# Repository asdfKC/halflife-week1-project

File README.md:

# Final design

### halflife-week1-project
For this project, I made a Macropad!

My components used are listed in BOM.md 

 This is an image of the 3d view of the PCB

This is an image of the PCB Gerber files!

This is my first pcb ever!

## GPIO USAGE:
It starts at GPIO0

## Key layout

| | Col 1 | Col 2 | Col 3 | Col 4 | Col 5 | Col 6 |
|---|---|---|---|---|---|---|
| **Row 1** | Ctrl+C | Ctrl+V | Ctrl+X | Ctrl+Z | Super+L | Mute |
| **Row 2** | Print Screen | F11 | Vol− | Vol+ | Up | Enter |
| **Row 3** | Previous | Play/Pause | Next | Left | Down | Right |

Switches are numbered SW1–SW18 and wired to GP0–GP17. Row 1 is SW1–SW6, row 2 is SW7, SW9, SW11, SW13, SW15, SW17, and row 3 is SW8, SW10, SW12, SW14, SW16, SW18.

The middle goes in numerical order.

## Firmware =D
The firmware is in 'firmware/code.py.' It uses KMK on CircuitPython.

## FLASHING INSTRUCTIONS
firmware/FLASHINSTRUCTIONS.md

## Switch plate :D

A pretty basic and simple plate is included in the plate/ directory. It has 18 cutouts that match the PCB, each the size of a standard MX switch cutout. The outline is in plate/Plates/plate_Edge_Cuts.dxf

I provided an STL file in the plate/ directory called plate.stl.

### Warnings

There are stray copper traces; however, they are dead and do not short the board in any way.

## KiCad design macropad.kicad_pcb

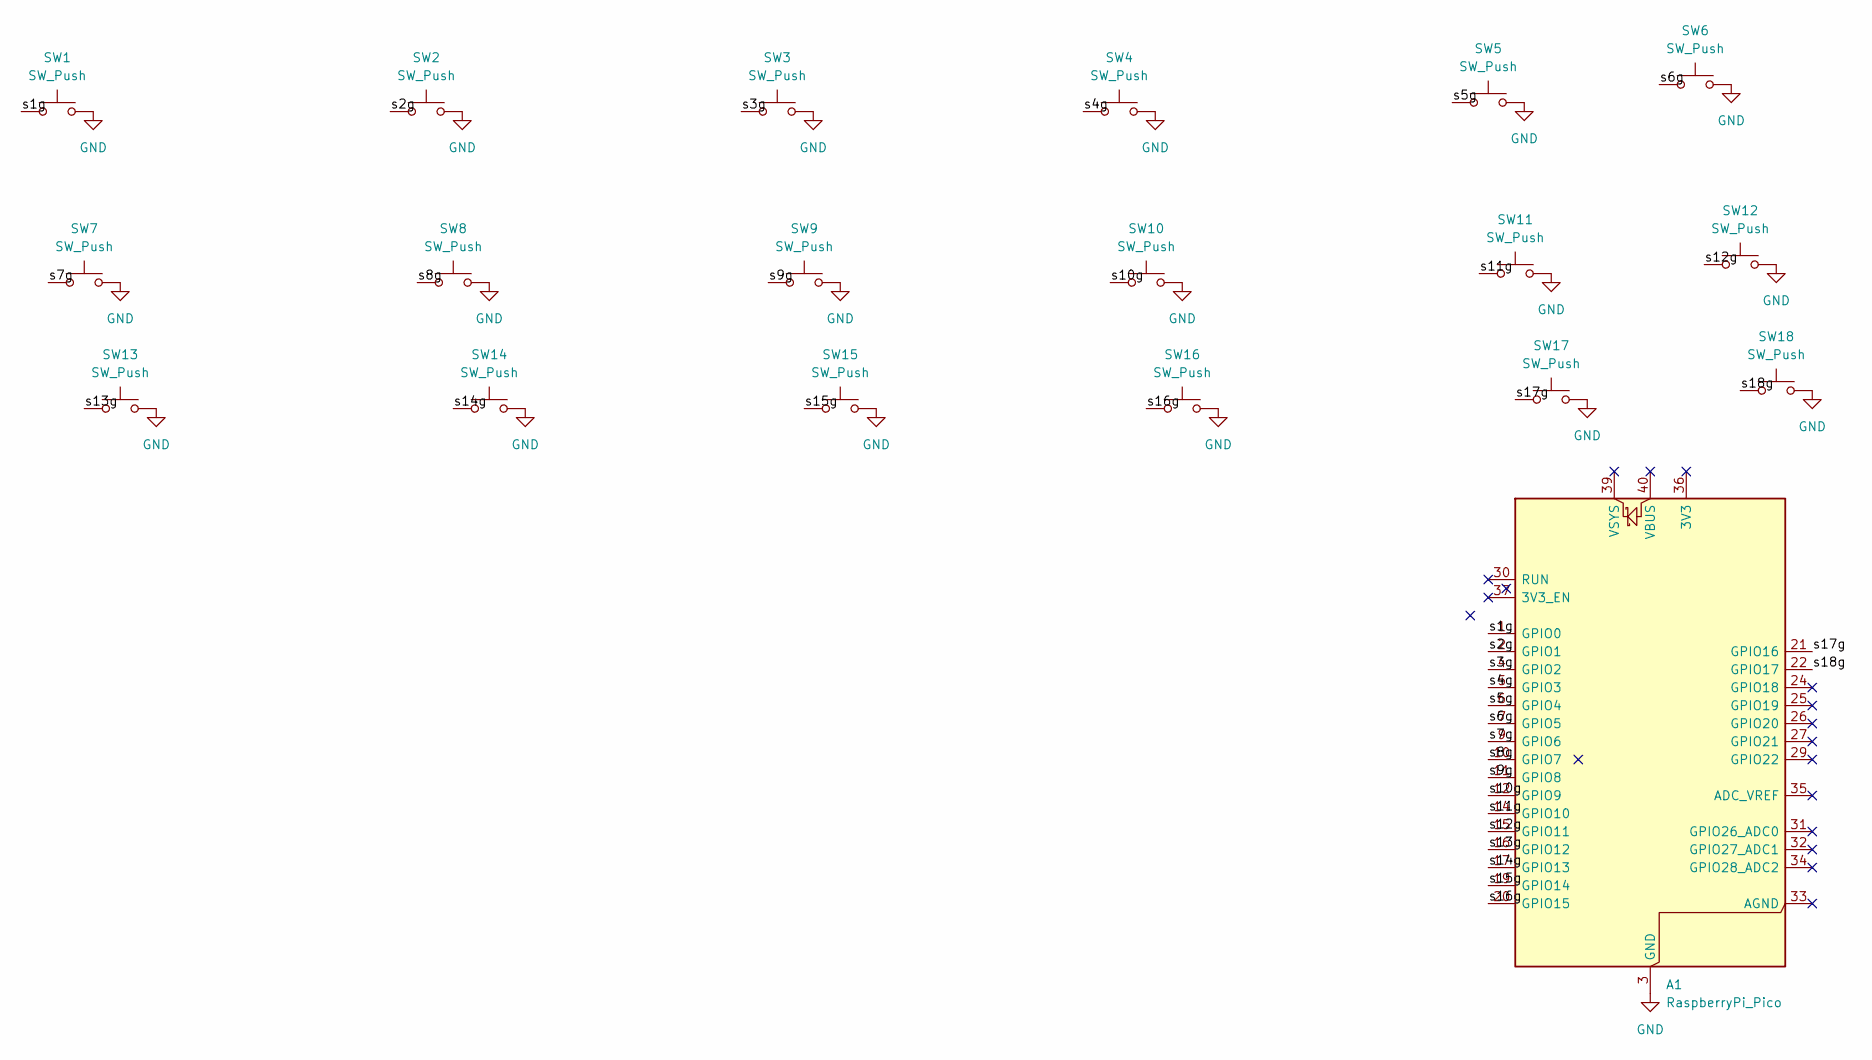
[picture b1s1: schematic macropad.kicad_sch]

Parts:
A1: RaspberryPi_Pico; RaspberryPi_Pico_Common_Unspecified
SW1, SW2, SW3, SW4, SW5, SW6, SW7, SW8, SW9, SW10, SW11, SW12, SW13, SW14, SW15, SW16, SW17, SW18: SW_Push; SW_Cherry_MX_1.00u_PCB

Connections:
/s1g: A1.1 (GPIO0), SW1.1
/s2g: A1.2 (GPIO1), SW2.1
/s3g: A1.4 (GPIO2), SW3.1
/s4g: A1.5 (GPIO3), SW4.1
/s5g: A1.6 (GPIO4), SW5.1
/s6g: A1.7 (GPIO5), SW6.1
/s7g: A1.9 (GPIO6), SW7.1
/s8g: A1.10 (GPIO7), SW8.1
/s9g: A1.11 (GPIO8), SW9.1
/s10g: A1.12 (GPIO9), SW10.1
/s11g: A1.14 (GPIO10), SW11.1
/s12g: A1.15 (GPIO11), SW12.1
/s13g: A1.16 (GPIO12), SW13.1
/s14g: A1.17 (GPIO13), SW14.1
/s15g: A1.19 (GPIO14), SW15.1
/s16g: A1.20 (GPIO15), SW16.1
/s17g: A1.21 (GPIO16), SW17.1
/s18g: A1.22 (GPIO17), SW18.1
GND: A1.3 (GND), A1.8 (GND), A1.13 (GND), A1.18 (GND), A1.23 (GND), A1.28 (GND), A1.38 (GND), SW1.2, SW2.2, SW3.2, SW4.2, SW5.2, SW6.2, SW7.2, SW8.2, SW9.2, SW10.2, SW11.2, SW12.2, SW13.2, SW14.2, SW15.2, SW16.2, SW17.2, SW18.2

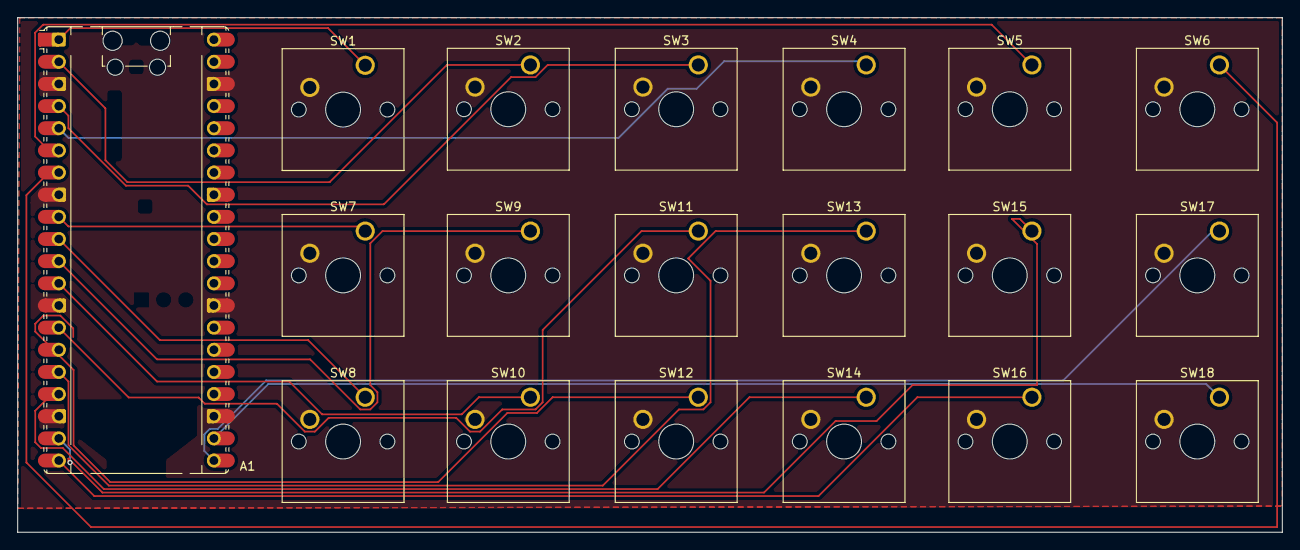
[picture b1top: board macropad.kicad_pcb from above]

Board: 2 copper layers, 145.0 x 59.0 mm, 19 parts (0 on the bottom side), 19 nets.
